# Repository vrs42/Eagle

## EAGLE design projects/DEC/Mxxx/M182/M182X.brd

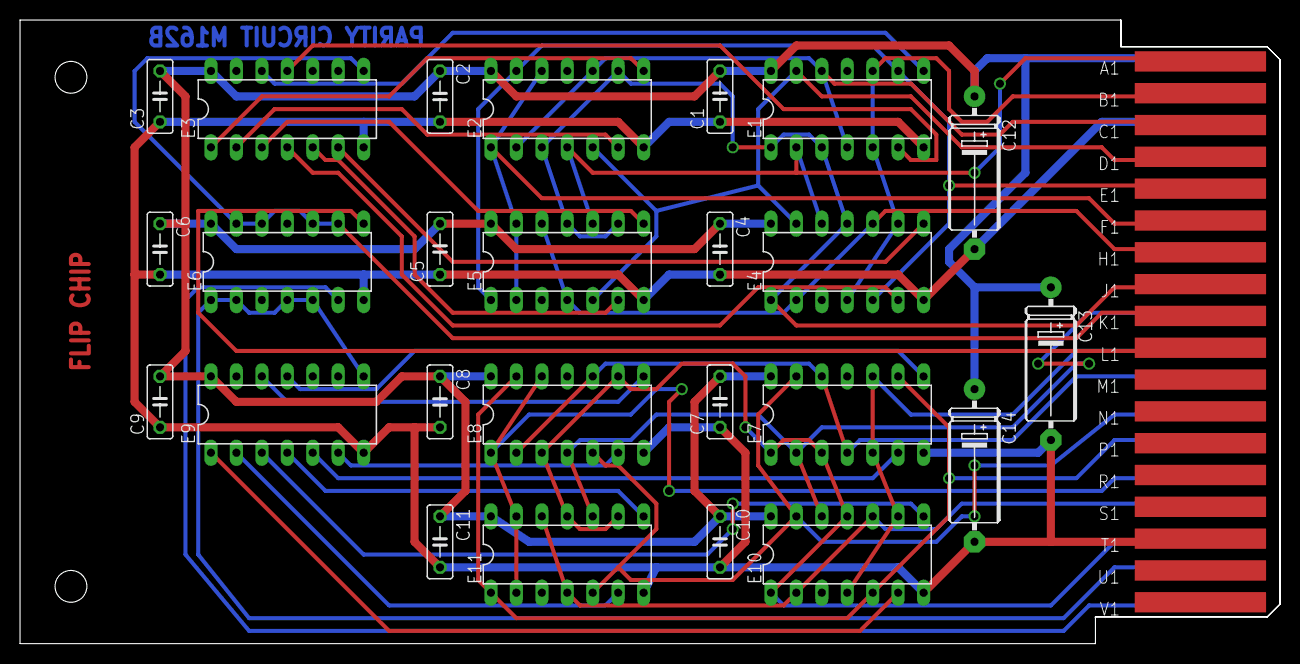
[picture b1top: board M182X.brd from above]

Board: 2 copper layers, 125.7 x 62.2 mm, 27 parts (0 on the bottom side), 38 nets.

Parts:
C1, C2, C3, C4, C5, C6, C7, C8, C9, C10, C11: .01uf; C050-025X075
C12, C13, C14: 6.8uf; E15-5
E1, E2, E4, E5, E6, E7, E8, E10, E11: 74H20N; DIL14
E3, E9: 74H30N; DIL14
U$1: OUTLINE-SINGLE; SINGLE
U$2: EDGE-CON2

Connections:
GND: C1.1, C2.2, C3.1, C4.2, C5.1, C6.2, C7.1, C8.2, C9.1, C10.2, C11.2, C12.-, C13.-, C14.-, E1.7, E2.7, E3.7, E4.7, E5.7, E6.7, E7.7, E8.7, E9.7, E10.7, E11.7, U$2.C2, U$2.T1
unnamed: E1.2, E2.4, E4.12, E5.10, U$2.A1
unnamed: E1.13, E2.5, E4.13, E5.5, U$2.D1
unnamed: E1.1, E1.3, E2.3, E2.9, E4.1, E4.11, E5.9, E5.11, U$2.J1
unnamed: E4.2, E4.10, E5.4, E5.12, U$2.H1
unnamed: E1.4, E1.12, E2.2, E2.10, U$2.C1
unnamed: E1.5, E1.10, E4.4, E4.9, U$2.B1
unnamed: E2.1, E2.12, E5.2, E5.13, U$2.F1
unnamed: E1.9, E2.13, E4.5, E5.1, U$2.E1
unnamed: E1.8, E3.12
unnamed: E3.4, E4.6
unnamed: E2.8, E3.1
unnamed: E3.5, E5.6
unnamed: E3.3, E5.8
unnamed: E2.6, E3.2
unnamed: E1.6, E3.11
unnamed: E3.6, E4.8
unnamed: E3.8, E6.9, E6.10, E6.12, E6.13, U$2.K1
unnamed: E7.2, E8.4, E10.12, E11.10, U$2.K2
unnamed: E7.13, E8.5, E10.13, E11.5, U$2.N2
unnamed: E7.1, E7.3, E8.3, E8.9, E10.1, E10.11, E11.9, E11.11, U$2.T2
unnamed: E10.2, E10.10, E11.4, E11.12, U$2.S2
unnamed: E7.4, E7.12, E8.2, E8.10, U$2.M2
unnamed: E7.5, E7.10, E10.4, E10.9, U$2.L2
unnamed: E8.1, E8.12, E11.2, E11.13, U$2.R2
unnamed: E7.9, E8.13, E10.5, E11.1, U$2.P2
unnamed: E7.8, E9.11
unnamed: E9.1, E10.6
unnamed: E8.8, E9.12
unnamed: E9.2, E11.6
unnamed: E9.4, E11.8
unnamed: E8.6, E9.6
unnamed: E7.6, E9.5
unnamed: E9.3, E10.8
unnamed: E6.1, E6.2, E6.4, E6.5, E9.8, U$2.U2
unnamed: E6.6, U$2.V2
unnamed: E6.8, U$2.L1
VCC: C1.2, C2.1, C3.2, C4.1, C5.2, C6.1, C7.2, C8.1, C9.2, C10.1, C11.1, C12.+, C13.+, C14.+, E1.14, E2.14, E3.14, E4.14, E5.14, E6.14, E7.14, E8.14, E9.14, E10.14, E11.14, U$2.A2

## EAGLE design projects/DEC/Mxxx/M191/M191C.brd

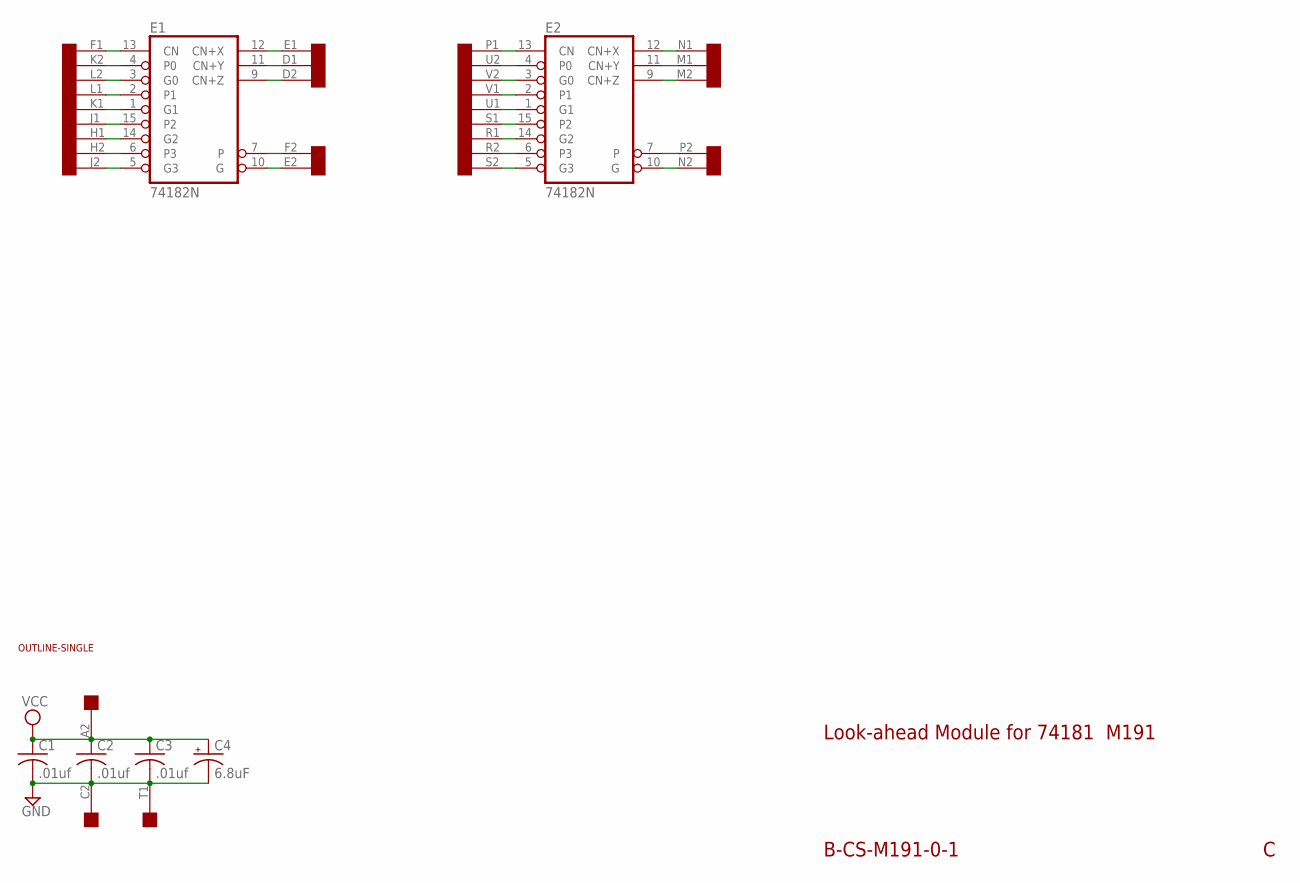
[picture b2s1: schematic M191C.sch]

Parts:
C1, C2, C3: .01uf; C050-025X075
C4: 6.8uF; E22-6
E1, E2: 74182N; DIL16
U$1: OUTLINE-SINGLE; SINGLE
U$2: EDGE-2CONNECTOR; EDGE-CON2

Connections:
GND: C1.2, C2.2, C3.2, C4.-, E1.8 (GND), E2.8 (GND), U$2.C2, U$2.T1
unnamed: E1.6 (P3), U$2.H2
unnamed: E1.2 (P1), U$2.L1
unnamed: E1.5 (G3), U$2.J2
unnamed: E1.15 (P2), U$2.J1
unnamed: E1.14 (G2), U$2.H1
unnamed: E1.1 (G1), U$2.K1
unnamed: E1.4 (P0), U$2.K2
unnamed: E1.3 (G0), U$2.L2
unnamed: E1.13 (CN), U$2.F1
unnamed: E1.7, U$2.F2
unnamed: E1.10 (G), U$2.E2
unnamed: E1.9 (CN+Z), U$2.D2
unnamed: E1.11 (CN+Y), U$2.D1
unnamed: E1.12 (CN+X), U$2.E1
unnamed: E2.13 (CN), U$2.P1
unnamed: E2.3 (G0), U$2.V2
unnamed: E2.4 (P0), U$2.U2
unnamed: E2.1 (G1), U$2.U1
unnamed: E2.2 (P1), U$2.V1
unnamed: E2.15 (P2), U$2.S1
unnamed: E2.14 (G2), U$2.R1
unnamed: E2.6 (P3), U$2.R2
unnamed: E2.5 (G3), U$2.S2
unnamed: E2.7, U$2.P2
unnamed: E2.10 (G), U$2.N2
unnamed: E2.9 (CN+Z), U$2.M2
unnamed: E2.11 (CN+Y), U$2.M1
unnamed: E2.12 (CN+X), U$2.N1
VCC: C1.1, C2.1, C3.1, C4.+, E1.16 (VCC), E2.16 (VCC), U$2.A2

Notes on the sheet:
B-CS-M191-0-1
Look-ahead Module for 74181 M191

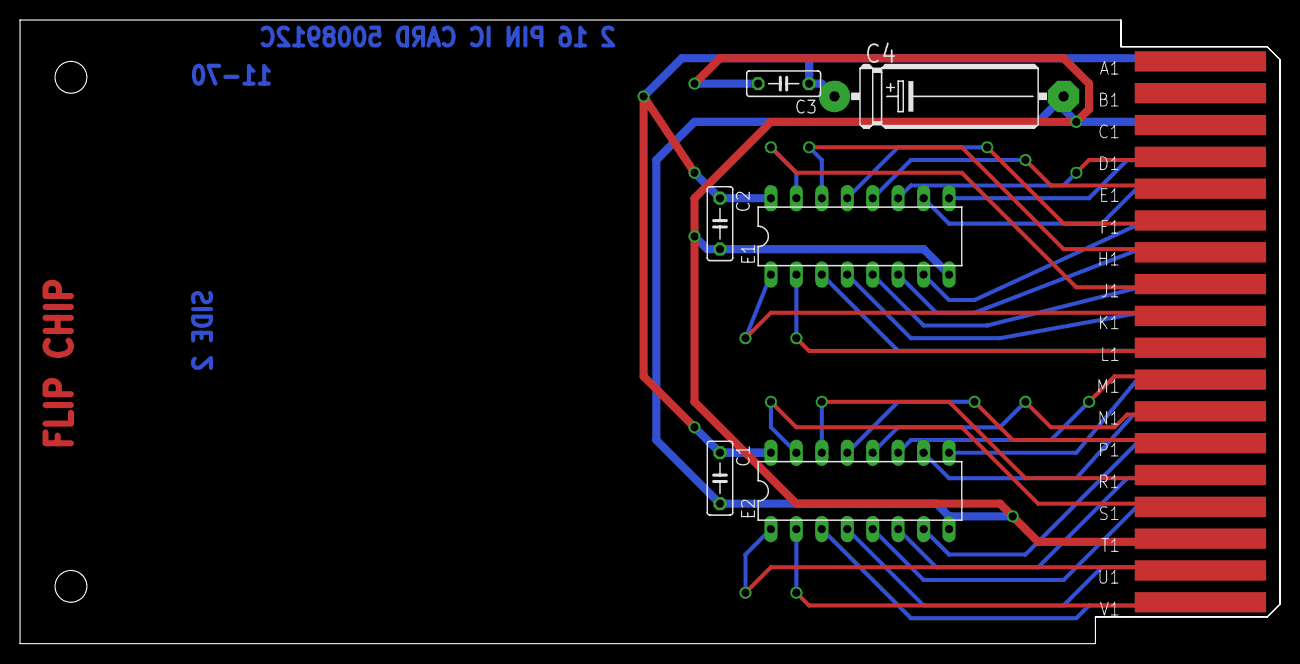
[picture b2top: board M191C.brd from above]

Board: 2 copper layers, 125.7 x 62.2 mm, 9 parts (0 on the bottom side), 30 nets.

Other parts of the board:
U$3: FLIPCHIP

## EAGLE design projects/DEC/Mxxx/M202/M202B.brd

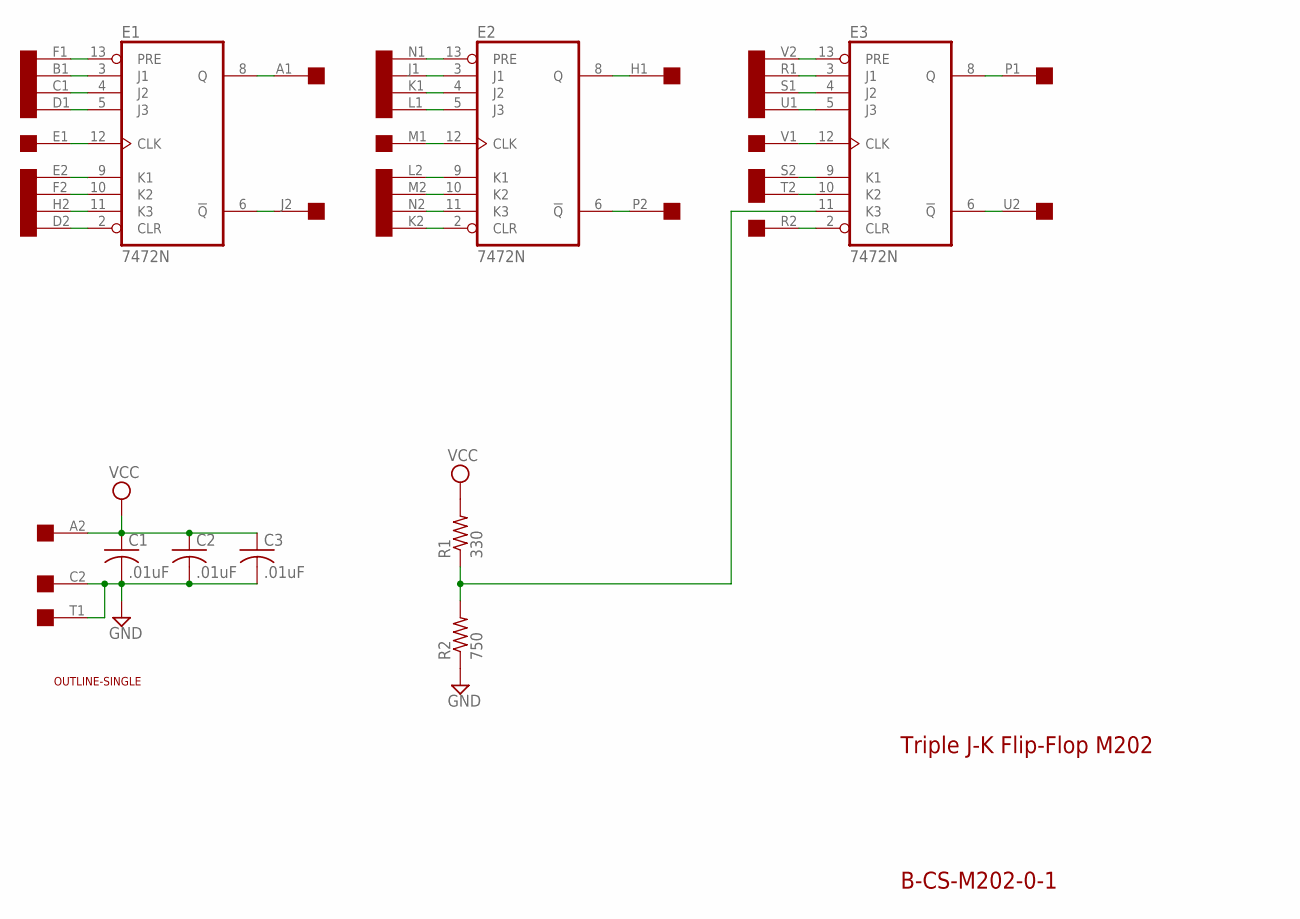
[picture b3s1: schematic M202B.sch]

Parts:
C1, C2, C3: .01uF; C050-025X075
E1, E2, E3: 7472N; DIL14
R1: 330; 0207/10
R2: 750; 0207/10
U$1: OUTLINE-SINGLE; SINGLE
U$2: SINGLE; EDGE-CON2

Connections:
A1: E1.8 (Q), U$2.A1
B1: E1.3 (J1), U$2.B1
C1: E1.4 (J2), U$2.C1
D1: E1.5 (J3), U$2.D1
D2: E1.2 (CLR), U$2.D2
E1: E1.12 (CLK), U$2.E1
E2: E1.9 (K1), U$2.E2
F1: E1.13 (PRE), U$2.F1
F2: E1.10 (K2), U$2.F2
GND: C1.2, C2.2, C3.2, E1.7 (GND), E2.7 (GND), E3.7 (GND), R2.1, U$2.C2, U$2.T1
H1: E2.8 (Q), U$2.H1
H2: E1.11 (K3), U$2.H2
J1: E2.3 (J1), U$2.J1
J2: E1.6 (!Q), U$2.J2
K1: E2.4 (J2), U$2.K1
K2: E2.2 (CLR), U$2.K2
L1: E2.5 (J3), U$2.L1
L2: E2.9 (K1), U$2.L2
M1: E2.12 (CLK), U$2.M1
M2: E2.10 (K2), U$2.M2
N1: E2.13 (PRE), U$2.N1
N2: E2.11 (K3), U$2.N2
unnamed: E3.11 (K3), R1.1, R2.2
P1: E3.8 (Q), U$2.P1
P2: E2.6 (!Q), U$2.P2
R1: E3.3 (J1), U$2.R1
R2: E3.2 (CLR), U$2.R2
S1: E3.4 (J2), U$2.S1
S2: E3.9 (K1), U$2.S2
T2: E3.10 (K2), U$2.T2
U1: E3.5 (J3), U$2.U1
U2: E3.6 (!Q), U$2.U2
V1: E3.12 (CLK), U$2.V1
V2: E3.13 (PRE), U$2.V2
VCC: C1.1, C2.1, C3.1, E1.14 (VCC), E2.14 (VCC), E3.14 (VCC), R1.2, U$2.A2

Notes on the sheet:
Triple J-K Flip-Flop M202
B-CS-M202-0-1

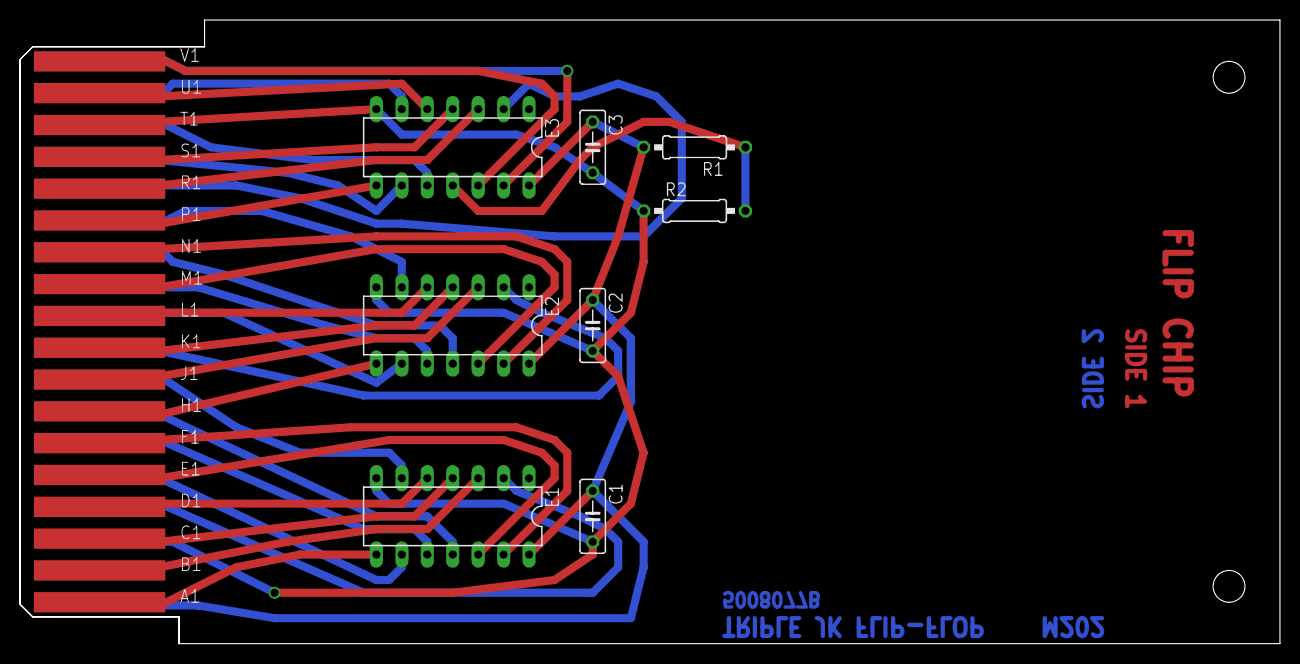
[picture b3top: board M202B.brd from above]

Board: 2 copper layers, 125.7 x 62.2 mm, 10 parts (0 on the bottom side), 35 nets.

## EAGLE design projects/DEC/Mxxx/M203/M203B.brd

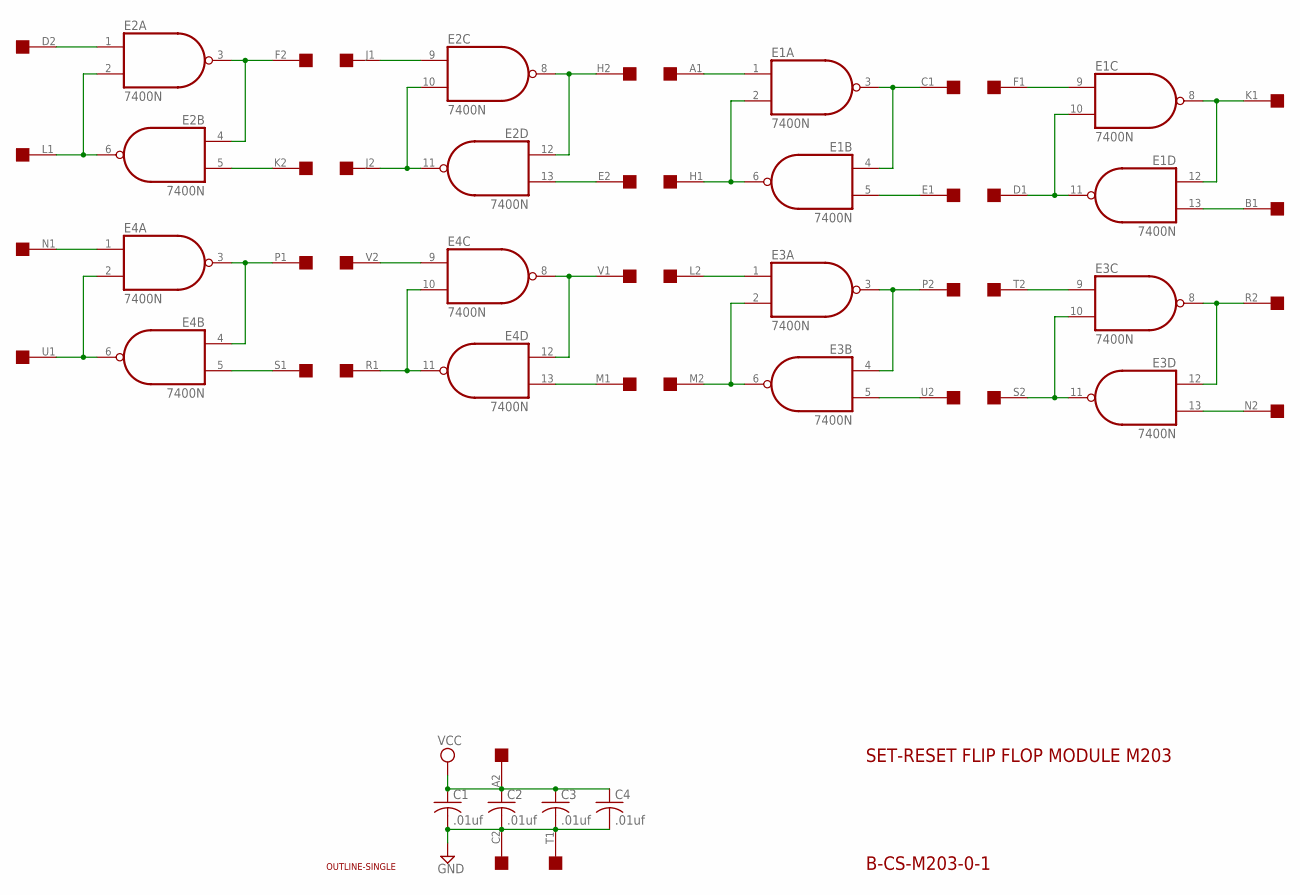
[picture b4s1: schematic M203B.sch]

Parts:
C1, C2, C3, C4: .01uf; C050-025X075
E1, E2, E3, E4: 7400N; DIL14
U$1: OUTLINE-SINGLE; SINGLE
U$2: EDGE-2CONNECTOR; EDGE-CON2

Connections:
GND: C1.2, C2.2, C3.2, C4.2, E1.7 (GND), E2.7 (GND), E3.7 (GND), E4.7 (GND), U$2.C2, U$2.T1
unnamed: E1.2 (I1), E1.6 (O), U$2.H1
unnamed: E1.3 (O), E1.4 (I0), U$2.C1
unnamed: E1.1 (I0), U$2.A1
unnamed: E1.5 (I1), U$2.E1
unnamed: E1.10 (I1), E1.11 (O), U$2.D1
unnamed: E1.8 (O), E1.12 (I0), U$2.K1
unnamed: E1.13 (I1), U$2.B1
unnamed: E1.9 (I0), U$2.F1
unnamed: E2.2 (I1), E2.6 (O), U$2.L1
unnamed: E2.3 (O), E2.4 (I0), U$2.F2
unnamed: E2.1 (I0), U$2.D2
unnamed: E2.5 (I1), U$2.K2
unnamed: E2.10 (I1), E2.11 (O), U$2.J2
unnamed: E2.8 (O), E2.12 (I0), U$2.H2
unnamed: E2.13 (I1), U$2.E2
unnamed: E2.9 (I0), U$2.J1
unnamed: E3.2 (I1), E3.6 (O), U$2.M2
unnamed: E3.3 (O), E3.4 (I0), U$2.P2
unnamed: E3.1 (I0), U$2.L2
unnamed: E3.5 (I1), U$2.U2
unnamed: E3.10 (I1), E3.11 (O), U$2.S2
unnamed: E3.8 (O), E3.12 (I0), U$2.R2
unnamed: E3.13 (I1), U$2.N2
unnamed: E3.9 (I0), U$2.T2
unnamed: E4.2 (I1), E4.6 (O), U$2.U1
unnamed: E4.3 (O), E4.4 (I0), U$2.P1
unnamed: E4.1 (I0), U$2.N1
unnamed: E4.5 (I1), U$2.S1
unnamed: E4.10 (I1), E4.11 (O), U$2.R1
unnamed: E4.8 (O), E4.12 (I0), U$2.V1
unnamed: E4.13 (I1), U$2.M1
unnamed: E4.9 (I0), U$2.V2
VCC: C1.1, C2.1, C3.1, C4.1, E1.14 (VCC), E2.14 (VCC), E3.14 (VCC), E4.14 (VCC), U$2.A2

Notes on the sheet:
B-CS-M203-0-1
SET-RESET FLIP FLOP MODULE M203

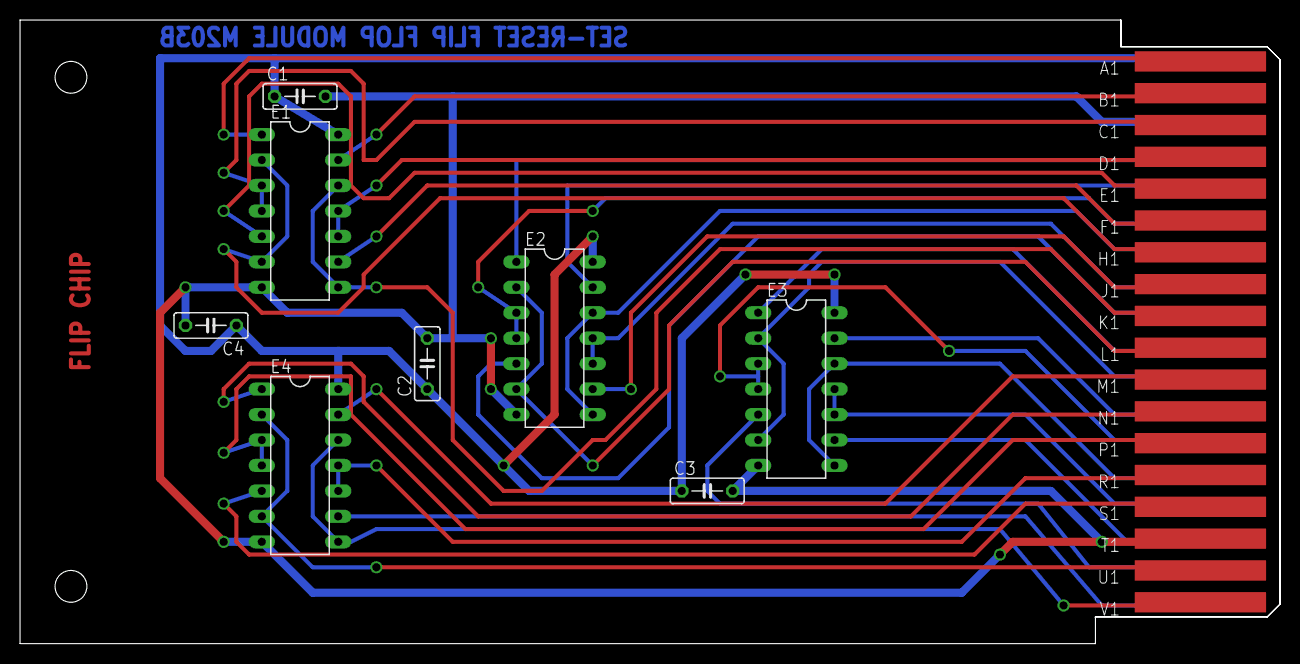
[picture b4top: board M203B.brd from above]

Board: 2 copper layers, 125.7 x 62.2 mm, 10 parts (0 on the bottom side), 34 nets.

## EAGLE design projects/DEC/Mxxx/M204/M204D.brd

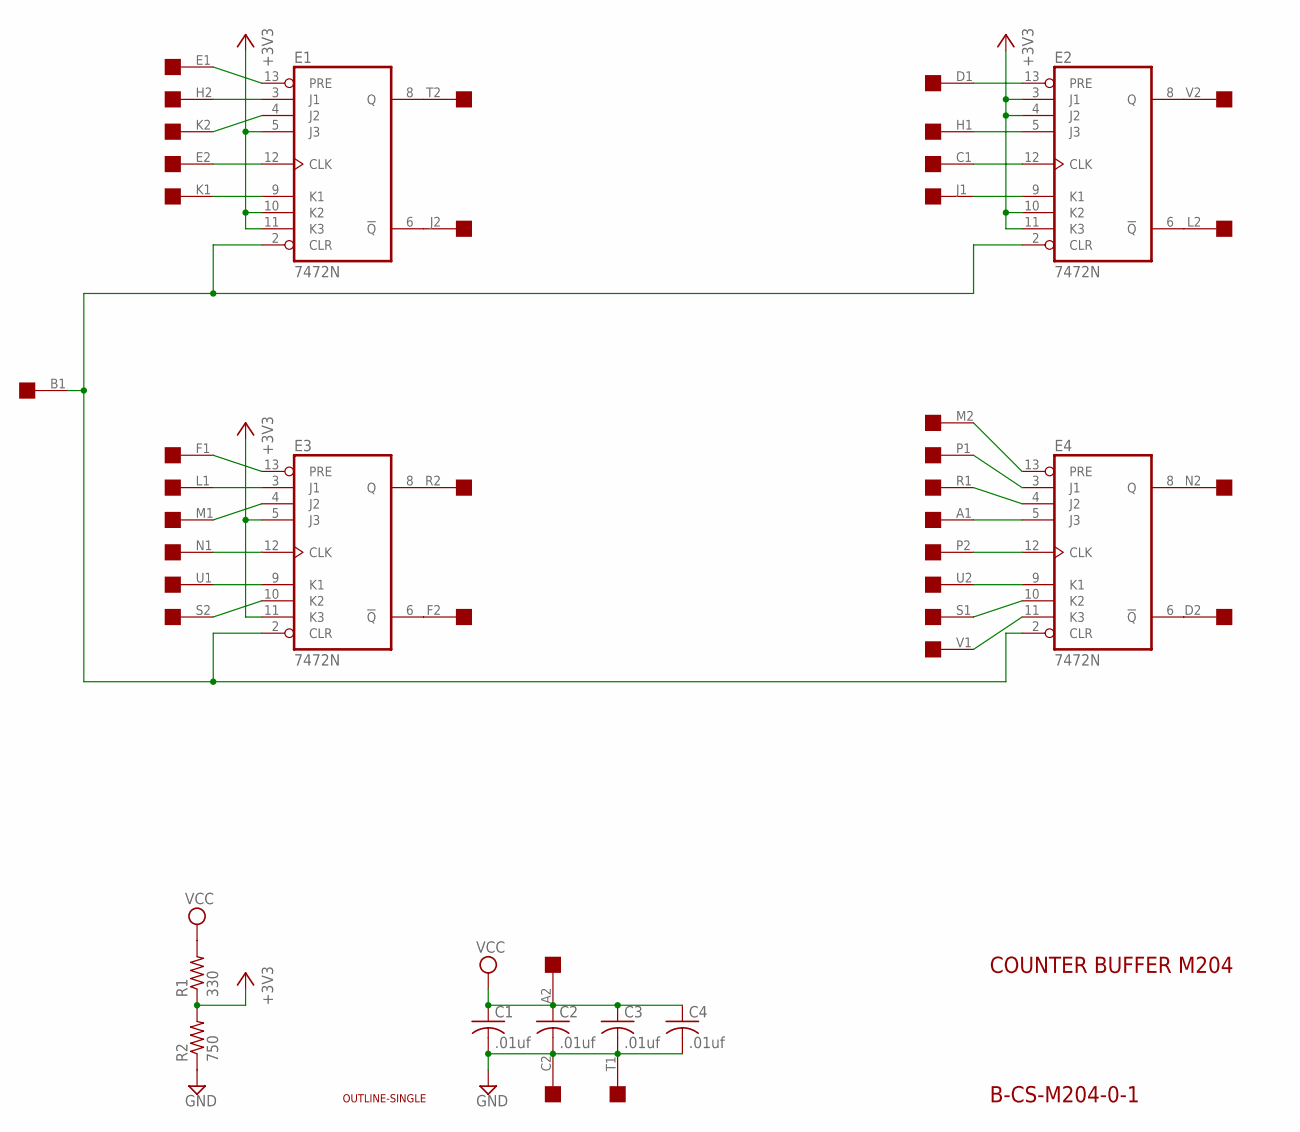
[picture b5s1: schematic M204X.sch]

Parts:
C1, C2, C3, C4: .01uf; C050-025X075
E1, E2, E3, E4: 7472N; DIL14
R1: 330; 0207/10
R2: 750; 0207/10
U$1: OUTLINE-SINGLE; SINGLE
U$2: EDGE-2CONNECTOR; EDGE-CON2

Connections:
+3V3: E1.5 (J3), E1.10 (K2), E1.11 (K3), E2.3 (J1), E2.4 (J2), E2.10 (K2), E2.11 (K3), E3.5 (J3), E3.11 (K3), R1.1, R2.2
GND: C1.2, C2.2, C3.2, C4.2, E1.7 (GND), E2.7 (GND), E3.7 (GND), E4.7 (GND), R2.1, U$2.C2, U$2.T1
unnamed: E2.13 (PRE), U$2.D1
unnamed: E1.2 (CLR), E2.2 (CLR), E3.2 (CLR), E4.2 (CLR), U$2.B1
unnamed: E2.5 (J3), U$2.H1
unnamed: E2.12 (CLK), U$2.C1
unnamed: E2.9 (K1), U$2.J1
unnamed: E2.6 (!Q), U$2.L2
unnamed: E2.8 (Q), U$2.V2
unnamed: E4.6 (!Q), U$2.D2
unnamed: E1.13 (PRE), U$2.E1
unnamed: E1.4 (J2), U$2.K2
unnamed: E1.6 (!Q), U$2.J2
unnamed: E1.12 (CLK), U$2.E2
unnamed: E1.9 (K1), U$2.K1
unnamed: E1.3 (J1), U$2.H2
unnamed: E1.8 (Q), U$2.T2
unnamed: E4.5 (J3), U$2.A1
unnamed: E3.9 (K1), U$2.U1
unnamed: E4.13 (PRE), U$2.M2
unnamed: E4.3 (J1), U$2.P1
unnamed: E4.4 (J2), U$2.R1
unnamed: E4.12 (CLK), U$2.P2
unnamed: E4.9 (K1), U$2.U2
unnamed: E4.11 (K3), U$2.V1
unnamed: E4.10 (K2), U$2.S1
unnamed: E4.8 (Q), U$2.N2
unnamed: E3.3 (J1), U$2.L1
unnamed: E3.4 (J2), U$2.M1
unnamed: E3.8 (Q), U$2.R2
unnamed: E3.6 (!Q), U$2.F2
unnamed: E3.10 (K2), U$2.S2
unnamed: E3.13 (PRE), U$2.F1
unnamed: E3.12 (CLK), U$2.N1
VCC: C1.1, C2.1, C3.1, C4.1, E1.14 (VCC), E2.14 (VCC), E3.14 (VCC), E4.14 (VCC), R1.2, U$2.A2

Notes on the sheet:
B-CS-M204-0-1
COUNTER BUFFER M204

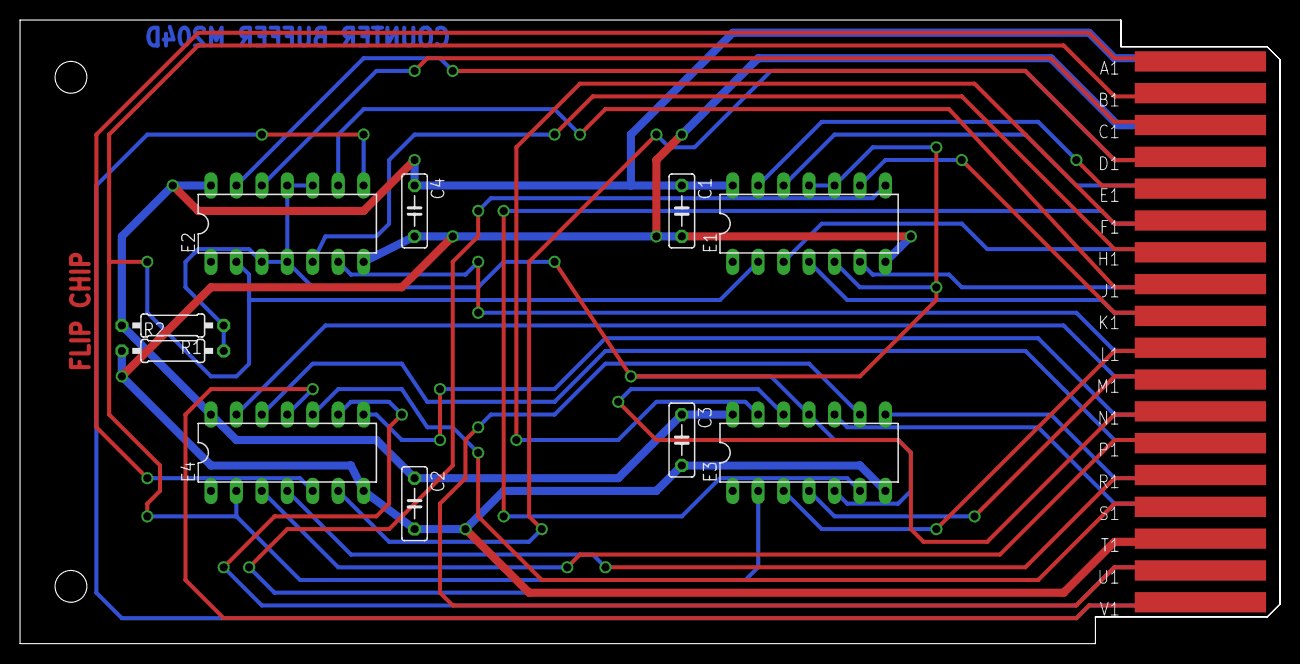
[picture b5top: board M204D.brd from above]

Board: 2 copper layers, 125.7 x 62.2 mm, 12 parts (0 on the bottom side), 35 nets.
